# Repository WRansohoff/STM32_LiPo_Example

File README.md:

# LiPo Battery-Powered STM32 Board

This is a small board which incorporates an `MCP73831` Lithium battery charger. It has a maximum charge rate of 500mA, but it is simple and easy to use. A JST PH-2 connector is used for the battery; it seems like small lithium batteries have more or less standardized on this type of connector, but double-check the polarity before you plug anything in.

A micro-USB plug is used as a 5V supply to charge the battery, and a small slide switch is used to turn the board's power on or off. Two 100KΩ resistors also form a voltage divider for the microcontroller to read the battery voltage through pin A0's ADC channel, and I'm planning to add an example firmware which reads and prints the battery voltage over UART in the near future.

This board will not work with the almost-identical `MCP73832` chip - the difference is that the 'status' pin has a tri-state output on the `MCP73831` and an open-drain output on the `MCP73832`. So with the former, you can have separate 'charging in progress' and 'done charging' LEDS. But with the latter, you can only have one 'done charging' LED directly connected to the pin. I dunno, maybe that saves you $.005 per unit when you order 10 million at a time or something.

# Board Renders

As seen through OSHPark's purple-colored glasses:

# Safety

**Before assembling this board or trying to incorporate elements into your design, spend some time ressearching lithium battery safety precautions. Always independently verify lithium battery circuits before assembling them. Never leave lithium batteries unattended when they are charging or in use.**

Here's a link to the datasheet for the battery-charging chip. Double-check your designs against its recommendations:

http://ww1.microchip.com/downloads/en/DeviceDoc/20001984g.pdf

I'm not even going to try to make a comprehensive list of safety precautions to take when handling lithium batteries, and working with circuitry that interacts with them is even more dangerous. Do your own research on how to work with them safely, start out with small batteries in the 100s of milliAmp-hours, and most importantly, don't blame me if anything goes wrong. The MIT license is very permissive, but it also says there's no warranty :)

# Future Work

* I should use a voltage regulator with a 'power good' pin and connect it to the reset line, to reduce problems with power supply glitches when the battery gets low.

* I haven't tested the USB data lines, and if they do work, there isn't much space to add the optional-but-recommended TVS diodes such as an `SP0503BAHT`. It might be better to use a cheaper microcontroller and only use the USB port for power.

* There's no "heartbeat" LED, and it's nice to have at least one user-controlled LED on a board for all kinds of reasons. For one thing, there's no way for the board to indicate that it has a low battery.

* I need to polish a simple test firmware which reads the battery voltage and prints it out over UART every few seconds.

* It's usually silly to use a linear voltage regulator in a simple battery-powered application, because you waste a bunch of power. Using a buck converter would be a better choice here.

* Per [#1](https://github.com/WRansohoff/STM32_LiPo_Example/issues/1), I should connect the `MCP73831` ground pin to a larger ground plane to help it dissipate heat and maybe reach its maximum charge current of 500mA.

* It might be a good idea to move the 'Ground' and '+Battery' breadboard pins farther apart, to make accidental shorts less likely.

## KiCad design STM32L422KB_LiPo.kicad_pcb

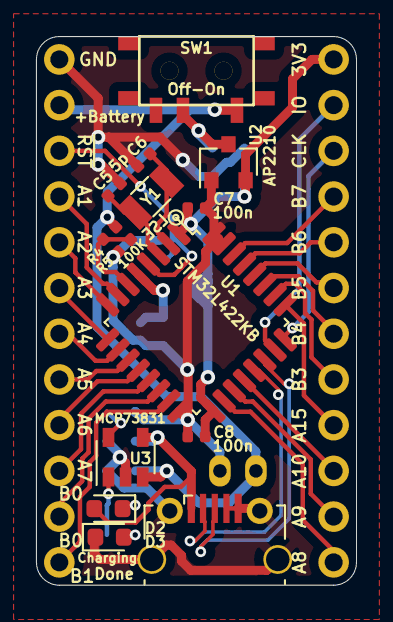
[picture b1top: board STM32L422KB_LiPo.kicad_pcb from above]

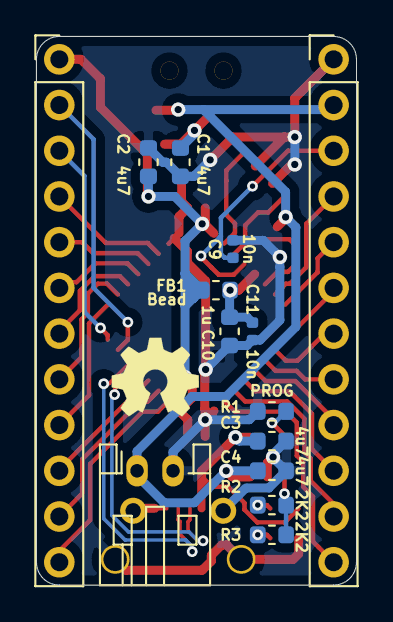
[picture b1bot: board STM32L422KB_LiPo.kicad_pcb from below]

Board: 2 copper layers, 17.8 x 30.5 mm, 28 parts (14 on the bottom side), 36 nets.

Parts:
C1, C2, C3, C4: 4u7; C_0603_1608Metric
C5, C6: 5p; C_0402_1005Metric
C7, C8: 100n; C_0402_1005Metric
C9, C11: 10n; C_0402_1005Metric
C10: 1u; C_0603_1608Metric
D2: Charging; LED_0603_1608Metric
D3: Done; LED_0603_1608Metric
FB1: Bead; R_0603_1608Metric
J1: uUSB; MyMicroUSB
J2: GPIO1; PinHeader_1x12_P2.54mm_Vertical
J3: GPIO2; PinHeader_1x12_P2.54mm_Vertical
J5: Battery; JST_PH_S2B-PH-K_1x02_P2.00mm_Horizontal
R1: PROG; R_0603_1608Metric
R2, R3: 2K2; R_0603_1608Metric
R4, R5: 100K; R_0402_1005Metric
SW1: Off-On; mini_slide_switch
U1: STM32L422KB; LQFP-32_7x7mm_P0.8mm
U2: AP2210; SOT-23
U3: MCP73831; SOT-23-5
Y1: LSE; Crystal_SMD_3215-2Pin_3.2x1.5mm

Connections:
+5V: C3.1, D2.2, J1.1, U3.4
+BATT: C4.1, J2.2, J5.1, R4.1, SW1.1, U3.3
A0: R4.2, R5.1, U1.6
A1: J2.4, U1.7
A2: J2.5, U1.8
A3: J2.6, U1.9
A4: J2.7, U1.10
A5: J2.8, U1.11
A6: J2.9, U1.12
A7: J2.10, U1.13
A8: J3.12, U1.18
A9: J3.11, U1.19
A10: J3.10, U1.20
A15: J3.9, U1.25
B0: J2.11, U1.14
B1: J2.12, U1.15
B3: J3.8, U1.26
B4: J3.7, U1.27
B5: J3.6, U1.28
B6: J3.5, U1.29
B7: J3.4, U1.30
GND: C1.1, C2.2, C3.2, C4.2, C5.2, C6.1, C7.2, C8.2, C9.2, C10.1, C11.2, D3.1, J1.4, J1.5, J1.6, J2.1, J5.2, R1.2, R5.2, U1.16, U1.31, U1.32, U2.1, U3.2
unnamed: C1.2, SW1.2, U2.3
unnamed: C5.1, U1.3, Y1.1
unnamed: C6.2, U1.2, Y1.2
unnamed: C10.2, C11.1, FB1.2, U1.5
unnamed: D2.1, R2.1
unnamed: D3.2, R3.1
unnamed: R1.1, U3.5
unnamed: R2.2, R3.2, U3.1
SWCLK: J3.3, U1.24
SWDIO: J3.2, U1.23
USB_D+: J1.3, U1.22
USB_D-: J1.2, U1.21
VDD: C2.1, C7.1, C8.1, FB1.1, J3.1, U1.1, U1.17, U2.2
~RST: C9.1, J2.3, U1.4

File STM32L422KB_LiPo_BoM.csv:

Part ID,Part type,Part size (Imperial),Part value,Example Digikey Item,Cost (qty: x),Comment
"C1, C2, C3, C4",Capacitor,0603,4.7 μF,https://www.digikey.com/short/p2hdqt,$0.68,Decoupling capacitors for the battery charger and voltage regulator. Use X5R or X7R ceramic capacitors rated for at least 6.3V
"C5, C6",Capacitor,0402,5 pF,https://www.digikey.com/short/pdhnbc,$0.20,Decoupling capacitors for the low-speed external oscillator crystal. Actual values will depend on your crystal; 5pF is a rough estimate. Use C0G / NP0 capacitors.
"C7, C8",Capacitor,0402,100 nF,https://www.digikey.com/short/p2hrz2,$0.20,Decoupling capacitors for the microcontroller / etc. Prefer X5 or X7 ceramic capacitors.
C10,Capacitor,0603,1 μF,https://www.digikey.com/short/pdhnbv,$0.10,Decoupling capacitor for the analog voltage supply. Use X7 ceramic capacitors.
"C9, C11",Capacitor,0402,10 nF,https://www.digikey.com/short/p2hr54,$0.20,Decoupling capacitors for the reset button and analog voltage supply. Use X7 ceramic capacitors.
FB1,Ferrite Bead,0603,N/A,https://www.digikey.com/short/p2h080,$0.10,Ferrite bead for filtering noise out of the analog voltage supply.
R1,Resistor,0603,">= 2 KΩ, 1%",https://www.digikey.com/short/pdh2b4,$0.10,"This resistor sets the rate of charge for the battery charger. Charge current = 1000 / R, so use 2KΩ for a 500mA charge rate, 10KΩ for a 100mA charge rate, etc. 500mA is the maximum charge rate. Use resistors with 1% precision to ensure you get the right charge rate."
"R2, R3",Resistor,0603,220Ω - 4.7KΩ,https://www.digikey.com/short/p2hdw9,$0.20,"Current-limiting resistors for the ""charging"" and ""done charging"" LEDs. Use higher values to make the LEDs dimmer."
"R4, R5",Resistor,0402,"100 KΩ, 1%",https://www.digikey.com/short/pdh2b7,$0.20,"Resistors for the voltage divider which lets the microcontroller read its own battery voltage. Use resistors with 1% precision, or choose two which have almost identical values."
J1,USB Connector,Micro-B Socket,N/A,https://www.digikey.com/short/pdhw81,$2.07,"Micro-USB connector for battery charging and USB communication. I'm still working through a reel of cheap-o micro-B sockets that I ordered awhile ago, but they seem to fit the ""Wuerth_629105150521"" footprint in KiCAD."
"J2, J3",Pin Header,"0.1""",1x12,https://www.digikey.com/short/p1rnnz,$0.60,"Pin headers for the board edges to plug into a breadboard. It's cheaper to bulk-order bunches of 1x40-row breakaway headers, but you can also order them in specific sizes."
SW1,Slide Switch,SMD,SPDT,https://www.digikey.com/short/pd2qtz,$0.91,Power on/off switch.
U1,Microcontroller,QFP-32 (7x7 mm),STM32L422KB,https://www.digikey.com/short/p1rdc0,$4.60,"I chose the STM32L422KB because it has a USB peripheral and can operate off of as little as 1.8V. But if you don't care about working USB, an STM32L0 chip would be cheaper. And if you don't care about low-voltage operation, an STM32F0x2 chip would be cheaper."
U2,Voltage Regulator,SOT-23,AP2210,https://www.digikey.com/short/p1rnv3,$0.42,Simple 3-pin 300mA 3.3V low-dropout linear regulator. They say that good things come in threes...
U3,Battery Charger,SOT-25,MCP73831,https://www.digikey.com/short/pdhw7v,$0.56,"Battery charging circuit. I use the 4.2V version with ""3.7V nominal / 4.2V charge"" lithium batteries."
Total,,,,,$11.14,

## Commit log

2019-12-16 Add initial readme and license file
2019-12-16 Add future improvements to the readme.
2019-12-16 Add initial KiCAD project files.
2019-12-16 Add project-specific schematic library and footprint files.
2019-12-16 Update readme's to-do list.
2019-12-16 Add a basic bill of materials for the board.
2019-12-16 Add initial board renders
2019-12-16 Move board renders to the same line.
2019-12-16 Add BoM entries for the LEDs and crystal oscillator.
2019-12-17 Add battery connector to the bill of materials.
2019-12-21 Add a to-do item to improve the battery charger's ability to dissipate heat into the board.
2019-12-21 Add to-do item to move ground/battery breadboard pins farther apart.
